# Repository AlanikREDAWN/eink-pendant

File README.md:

# eink Pendant

It's a PCB! No wait, its a keychain! Actually, its both. 

The idea for this PCB is, you press a button, and it changes the LED color and the image displayed on the eink display. It's a pretty simple concept, but I still enjoyed making it :)

## BOM
| Item                                      | Qty | Unit Price | Total Price | Product Link                                                                                                                                                                                                                       |
| ----------------------------------------- | --- | ---------- | ----------- | ---------------------------------------------------------------------------------------------------------------------------------------------------------------------------------------------------------------------------------- |
| Seeed Studio XIAO RP2040                  | 1   | $3.79      | $3.79       | [https://www.seeedstudio.com/XIAO-RP2040-v1-0-p-5026.html](https://www.seeedstudio.com/XIAO-RP2040-v1-0-p-5026.html)                                                                                                               |
| 2.9" Monochrome eInk / ePaper Display     | 1   | $9.99      | $9.99       | [https://www.seeedstudio.com/2-9-Monochrome-ePaper-Display-with-296x128-Pixels-p-5782.html](https://www.seeedstudio.com/2-9-Monochrome-ePaper-Display-with-296x128-Pixels-p-5782.html)                                             |
| ePaper Driver Board for Seeed Studio XIAO | 1   | $4.66      | $4.66       | [https://www.seeedstudio.com/ePaper-breakout-Board-for-XIAO-V2-p-6374.html](https://www.seeedstudio.com/ePaper-breakout-Board-for-XIAO-V2-p-6374.html)                                                                             |
| Cherry MX Blue Clicky RGB Switches        | 10  | $0.445     | $4.45       | [https://www.thockking.com/products/cherry-mx-blue-rgb-switches?variant=42102661087448](https://www.thockking.com/products/cherry-mx-blue-rgb-switches?variant=42102661087448)                                                     |
| NeoPixel Diffused 5mm Through-Hole LED    | 1   | $4.95      | $4.95       | [https://www.digikey.com/en/products/detail/adafruit-industries-llc/1938/6827082](https://www.digikey.com/en/products/detail/adafruit-industries-llc/1938/6827082)                                                                 |
| 330 Ohm Metal Film Resistor               | 5   | $0.10      | $0.50       | [https://www.digikey.com/en/products/detail/koa-speer-electronics-inc/MF1-4LCT52R331J/21679525](https://www.digikey.com/en/products/detail/koa-speer-electronics-inc/MF1-4LCT52R331J/21679525)                                     |
| 3.7V Lipo Battery                         | 1   | $8.99      | $8.99       | [https://www.amazon.com/Qimoo-Battery-Rechargeable-Connector-Electronic/dp/B0CNLPBM2L?nsdOptOutParam=true&sr=8-7](https://www.amazon.com/Qimoo-Battery-Rechargeable-Connector-Electronic/dp/B0CNLPBM2L?nsdOptOutParam=true&sr=8-7) |
| PCB                                       | 5   | N/A        | $2.00       | N/A                                                                                                                                                                                                                                |
 
## Cart Screenshots

## Screenshots

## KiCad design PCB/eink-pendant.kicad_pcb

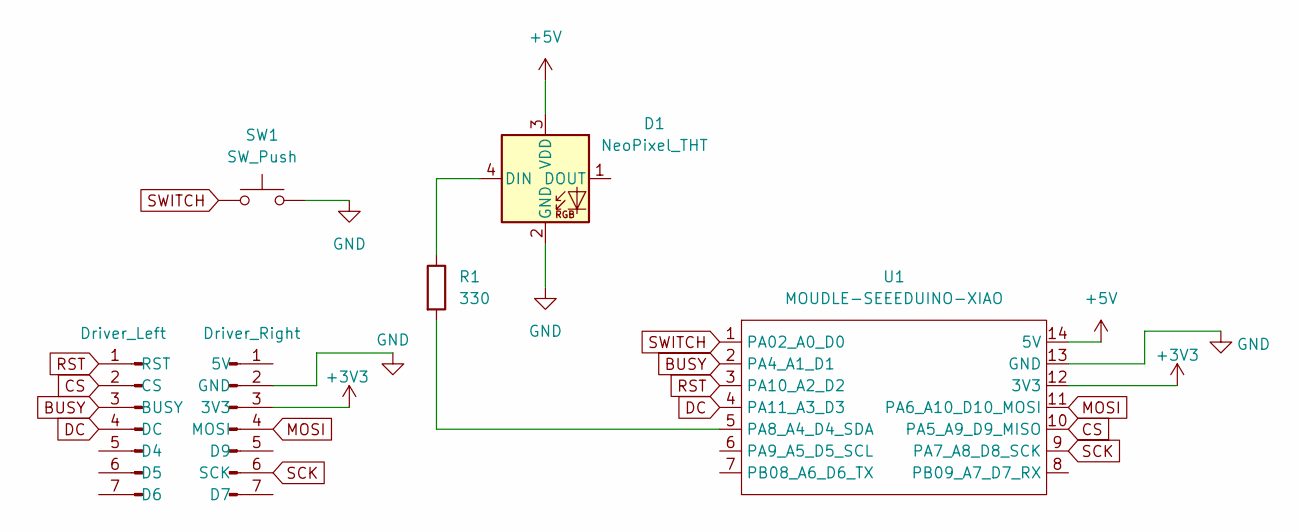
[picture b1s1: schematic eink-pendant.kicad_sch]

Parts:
D1: NeoPixel_THT; LED_D5.0mm-4_RGB
J3: Driver_Right; PinHeader_1x07_P2.54mm_Vertical
J4: Driver_Left; PinHeader_1x07_P2.54mm_Vertical
R1: 330; R_Axial_DIN0207_L6.3mm_D2.5mm_P7.62mm_Horizontal
SW1: SW_Push; SW_Cherry_MX_1.00u_PCB
U1: MOUDLE-SEEEDUINO-XIAO; XIAO-RP2040-DIP

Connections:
+3V3: J3.3 (3V3), U1.12 (3V3)
+5V: D1.3 (VDD), U1.14 (5V)
BUSY: J4.3 (BUSY), U1.2 (PA4_A1_D1)
CS: J4.2 (CS), U1.10 (PA5_A9_D9_MISO)
DC: J4.4 (DC), U1.4 (PA11_A3_D3)
GND: D1.2 (GND), J3.2 (GND), SW1.2, U1.13 (GND)
MOSI: J3.4 (MOSI), U1.11 (PA6_A10_D10_MOSI)
unnamed: D1.4 (DIN), R1.1
unnamed: R1.2, U1.5 (PA8_A4_D4_SDA)
RST: J4.1 (RST), U1.3 (PA10_A2_D2)
SCK: J3.6 (SCK), U1.9 (PA7_A8_D8_SCK)
SWITCH: SW1.1, U1.1 (PA02_A0_D0)

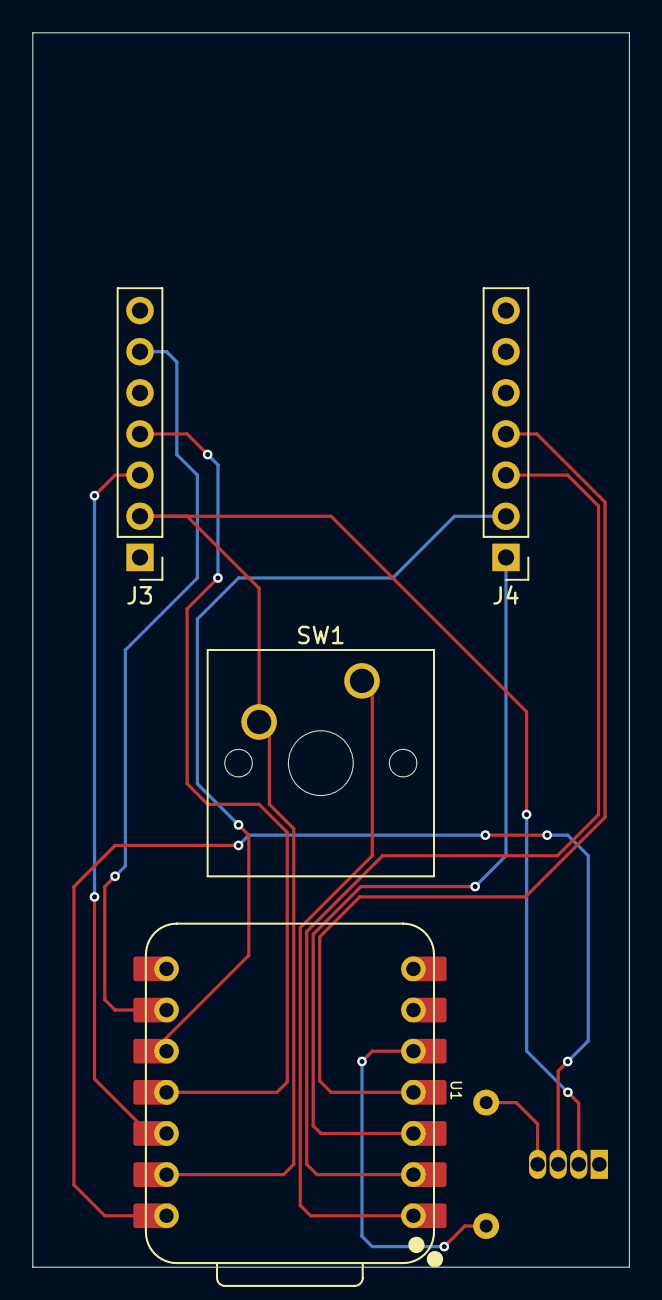
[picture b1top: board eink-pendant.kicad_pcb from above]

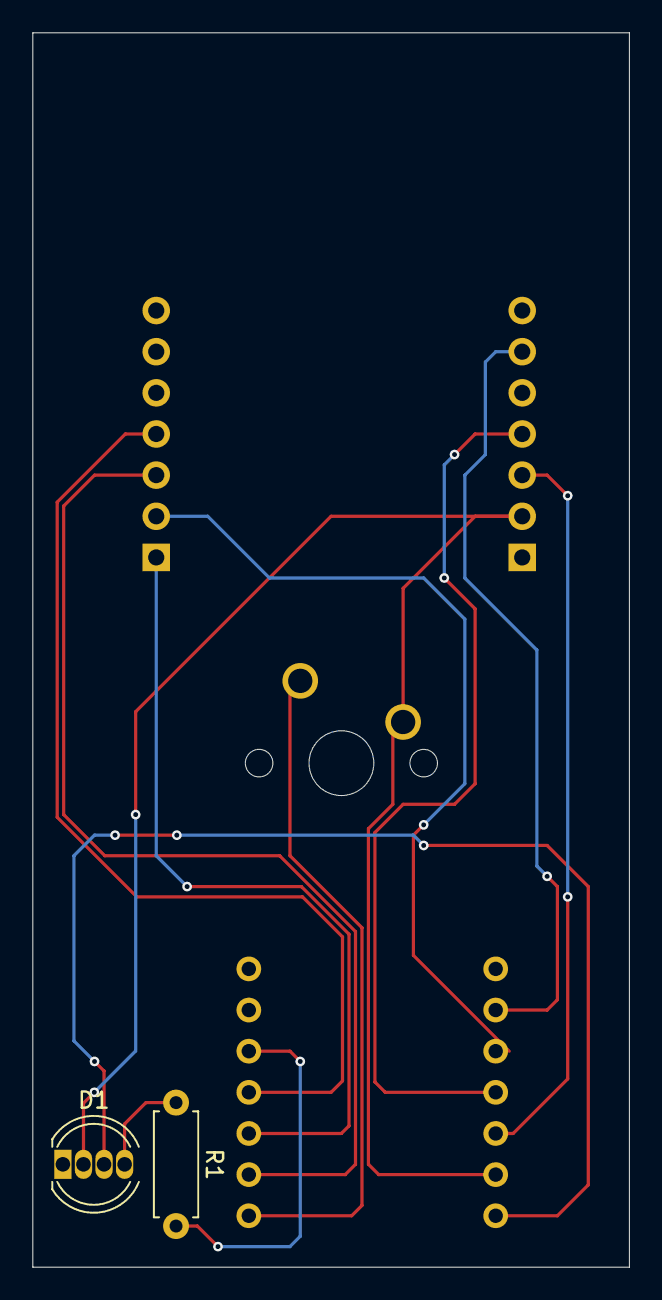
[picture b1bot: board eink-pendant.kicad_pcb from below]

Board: 2 copper layers, 36.8 x 76.2 mm, 6 parts (2 on the bottom side), 12 nets.

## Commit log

2026-06-17 updating journal
2026-06-17 small edit
2026-06-17 updating journal.md
2026-06-19 adding screenshots for readme
2026-06-19 stuffs
2026-06-19 README
    Added project description and features for eink Pendant.
2026-06-19 readme
2026-06-19 add PCB to BOM
